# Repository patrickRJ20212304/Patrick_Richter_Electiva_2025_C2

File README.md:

# Patrick_Richter_Electiva_2025_C2

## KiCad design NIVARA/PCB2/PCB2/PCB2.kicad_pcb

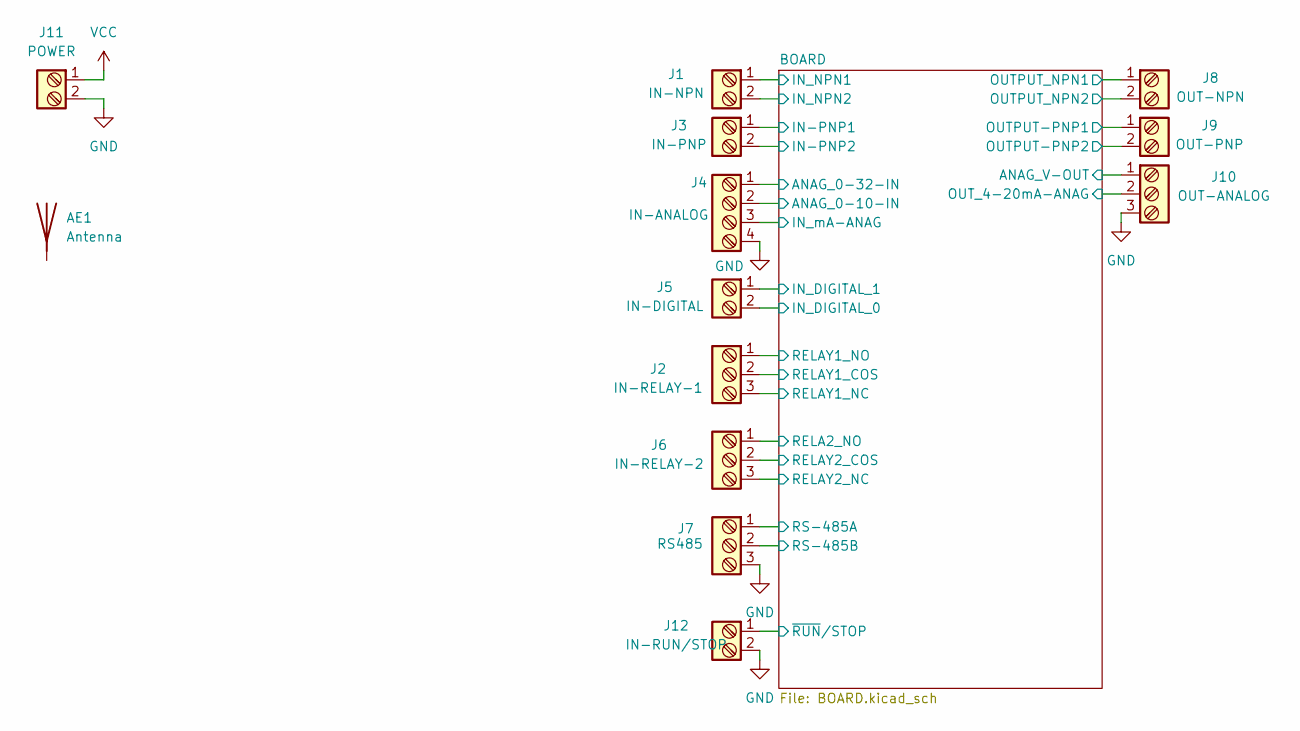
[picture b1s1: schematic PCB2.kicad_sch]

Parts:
AE1: Antenna
J1: IN-NPN; TerminalBlock_Phoenix_PT-1,5-2-5.0-H_1x02_P5.00mm_Horizontal
J2: IN-RELAY-1; TerminalBlock_Phoenix_PT-1,5-3-5.0-H_1x03_P5.00mm_Horizontal
J3: IN-PNP; TerminalBlock_Phoenix_PT-1,5-2-5.0-H_1x02_P5.00mm_Horizontal
J4: IN-ANALOG; TerminalBlock_Phoenix_PT-1,5-4-5.0-H_1x04_P5.00mm_Horizontal
J5: IN-DIGITAL; TerminalBlock_Phoenix_PT-1,5-2-5.0-H_1x02_P5.00mm_Horizontal
J6: IN-RELAY-2; TerminalBlock_Phoenix_PT-1,5-3-5.0-H_1x03_P5.00mm_Horizontal
J7: RS485; TerminalBlock_Phoenix_PT-1,5-3-5.0-H_1x03_P5.00mm_Horizontal
J8: OUT-NPN; TerminalBlock_Phoenix_PT-1,5-2-5.0-H_1x02_P5.00mm_Horizontal
J9: OUT-PNP; TerminalBlock_Phoenix_PT-1,5-2-5.0-H_1x02_P5.00mm_Horizontal
J10: OUT-ANALOG; TerminalBlock_Phoenix_PT-1,5-3-5.0-H_1x03_P5.00mm_Horizontal
J11: POWER; TerminalBlock_Phoenix_PT-1,5-2-5.0-H_1x02_P5.00mm_Horizontal
J12: IN-RUN/STOP; TerminalBlock_Phoenix_PT-1,5-2-5.0-H_1x02_P5.00mm_Horizontal

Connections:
/ANAG_V-OUT: J10.1
/BOARD/ANAG_0-10-IN: J4.2; also elsewhere on the board
/BOARD/ANAG_0-32-IN: J4.1; also elsewhere on the board
/BOARD/IN-PNP1: J3.1; also elsewhere on the board
/BOARD/IN-PNP2: J3.2; also elsewhere on the board
/BOARD/IN_DIGITAL_0: J5.2; also elsewhere on the board
/BOARD/IN_DIGITAL_1: J5.1; also elsewhere on the board
/BOARD/IN_NPN1: J1.1; also elsewhere on the board
/BOARD/IN_NPN2: J1.2; also elsewhere on the board
/BOARD/IN_mA-ANAG: J4.3; also elsewhere on the board
/BOARD/OUTPUT-PNP1: J9.1; also elsewhere on the board
/BOARD/OUTPUT-PNP2: J9.2; also elsewhere on the board
/BOARD/OUTPUT_NPN1: J8.1; also elsewhere on the board
/BOARD/OUTPUT_NPN2: J8.2; also elsewhere on the board
/BOARD/OUT_4-20mA-ANAG: J10.2; also elsewhere on the board
/BOARD/RELA2_NO: J6.1; also elsewhere on the board
/BOARD/RELAY1_COS: J2.2; also elsewhere on the board
/BOARD/RELAY1_NC: J2.3; also elsewhere on the board
/BOARD/RELAY1_NO: J2.1; also elsewhere on the board
/BOARD/RELAY2_COS: J6.2; also elsewhere on the board
/BOARD/RELAY2_NC: J6.3; also elsewhere on the board
/BOARD/RS-485A: J7.1; also elsewhere on the board
/BOARD/RS-485B: J7.2; also elsewhere on the board
/BOARD/~RUN/STOP: J12.1; also elsewhere on the board
GND: J4.4, J7.3, J10.3, J11.2, J12.2; also elsewhere on the board
VCC: J11.1; also elsewhere on the board

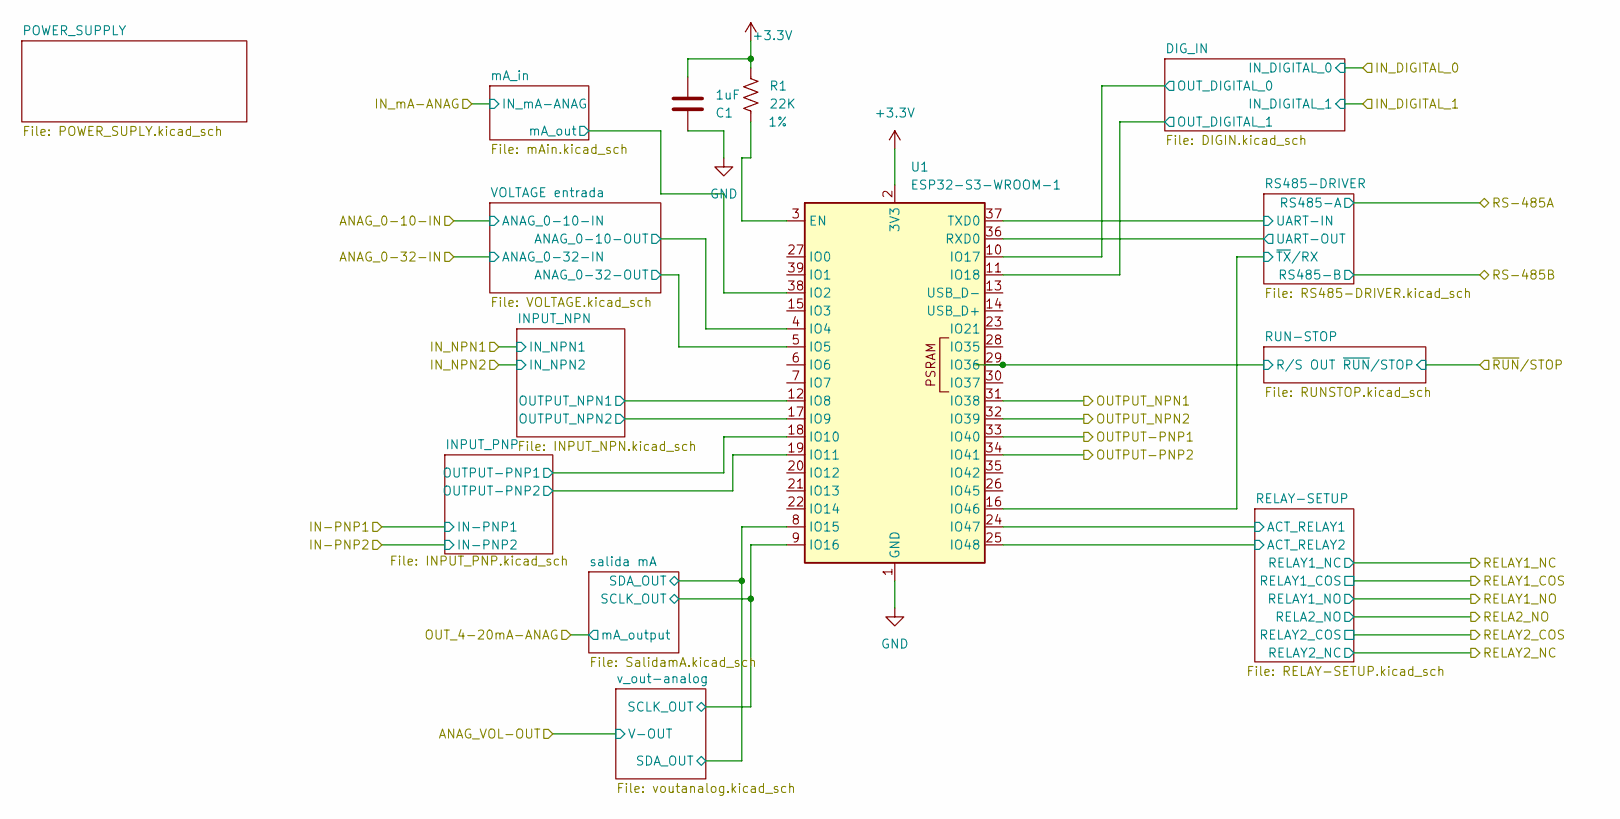
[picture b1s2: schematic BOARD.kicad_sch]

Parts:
C1: 1uF; C_0603_1608Metric; Voltage 10V
R1: 22K; R_0603; Tolerance 1%
U1: ESP32-S3-WROOM-1

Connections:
+3.3V: C1.2, R1.1, U1.2 (3V3); also elsewhere on the board
/BOARD/DIG_IN/OUT_DIGITAL_0: U1.10 (IO17); also elsewhere on the board
/BOARD/DIG_IN/OUT_DIGITAL_1: U1.11 (IO18); also elsewhere on the board
/BOARD/INPUT_NPN/OUTPUT_NPN1: U1.12 (IO8); also elsewhere on the board
/BOARD/INPUT_NPN/OUTPUT_NPN2: U1.17 (IO9); also elsewhere on the board
/BOARD/INPUT_PNP/OUTPUT-PNP1: U1.18 (IO10); also elsewhere on the board
/BOARD/INPUT_PNP/OUTPUT-PNP2: U1.19 (IO11); also elsewhere on the board
/BOARD/IN_mA-ANAG: U1.38 (IO2); also elsewhere on the board
/BOARD/OUTPUT-PNP1: U1.33 (IO40); also elsewhere on the board
/BOARD/OUTPUT-PNP2: U1.34 (IO41); also elsewhere on the board
/BOARD/OUTPUT_NPN1: U1.31 (IO38); also elsewhere on the board
/BOARD/OUTPUT_NPN2: U1.32 (IO39); also elsewhere on the board
/BOARD/RELAY-SETUP/ACT_RELAY1: U1.24 (IO47); also elsewhere on the board
/BOARD/RELAY-SETUP/ACT_RELAY2: U1.25 (IO48); also elsewhere on the board
/BOARD/RS485-DRIVER/UART-IN: U1.37 (TXD0); also elsewhere on the board
/BOARD/RS485-DRIVER/UART-OUT: U1.36 (RXD0); also elsewhere on the board
/BOARD/RS485-DRIVER/~TX/RX: U1.16 (IO46); also elsewhere on the board
/BOARD/VOLTAGE entrada/ANAG_0-10-OUT: U1.4 (IO4); also elsewhere on the board
/BOARD/VOLTAGE entrada/ANAG_0-32-OUT: U1.5 (IO5); also elsewhere on the board
/BOARD/salida mA/SCLK_OUT: U1.9 (IO16); also elsewhere on the board
/BOARD/salida mA/SDA_OUT: U1.8 (IO15); also elsewhere on the board
/BOARD/~RUN/STOP: U1.29 (IO36); also elsewhere on the board
GND: C1.1, U1.1 (GND), U1.40 (GND), U1.41 (GND); also elsewhere on the board
unnamed: R1.2, U1.3 (EN)

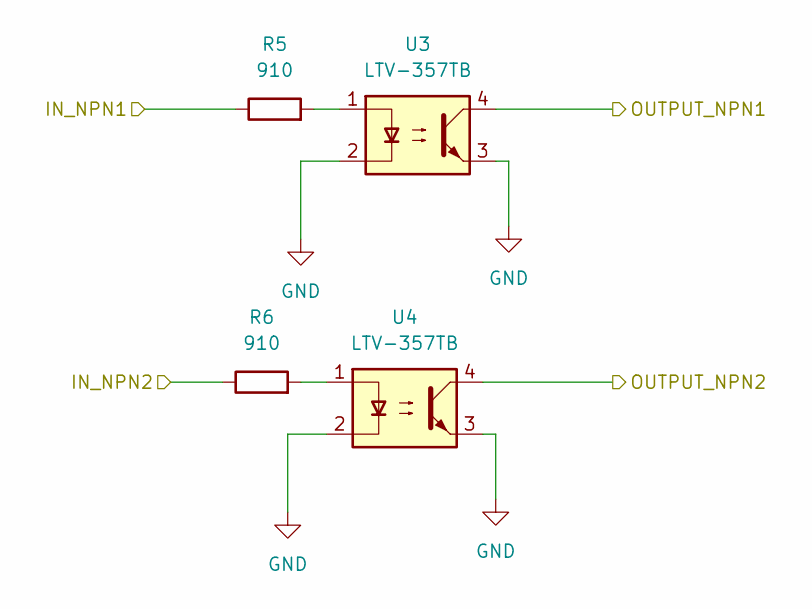
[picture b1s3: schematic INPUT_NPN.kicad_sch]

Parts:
R5, R6: 910; R_0603_1608Metric; LCSC# C114670
U3, U4: LTV-357TB; SO-4_4.4x3.6mm_P2.54mm

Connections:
/BOARD/INPUT_NPN/OUTPUT_NPN1: U3.4; also elsewhere on the board
/BOARD/INPUT_NPN/OUTPUT_NPN2: U4.4; also elsewhere on the board
/BOARD/IN_NPN1: R5.1; also elsewhere on the board
/BOARD/IN_NPN2: R6.1; also elsewhere on the board
GND: U3.2, U3.3, U4.2, U4.3; also elsewhere on the board
unnamed: R5.2, U3.1
unnamed: R6.2, U4.1

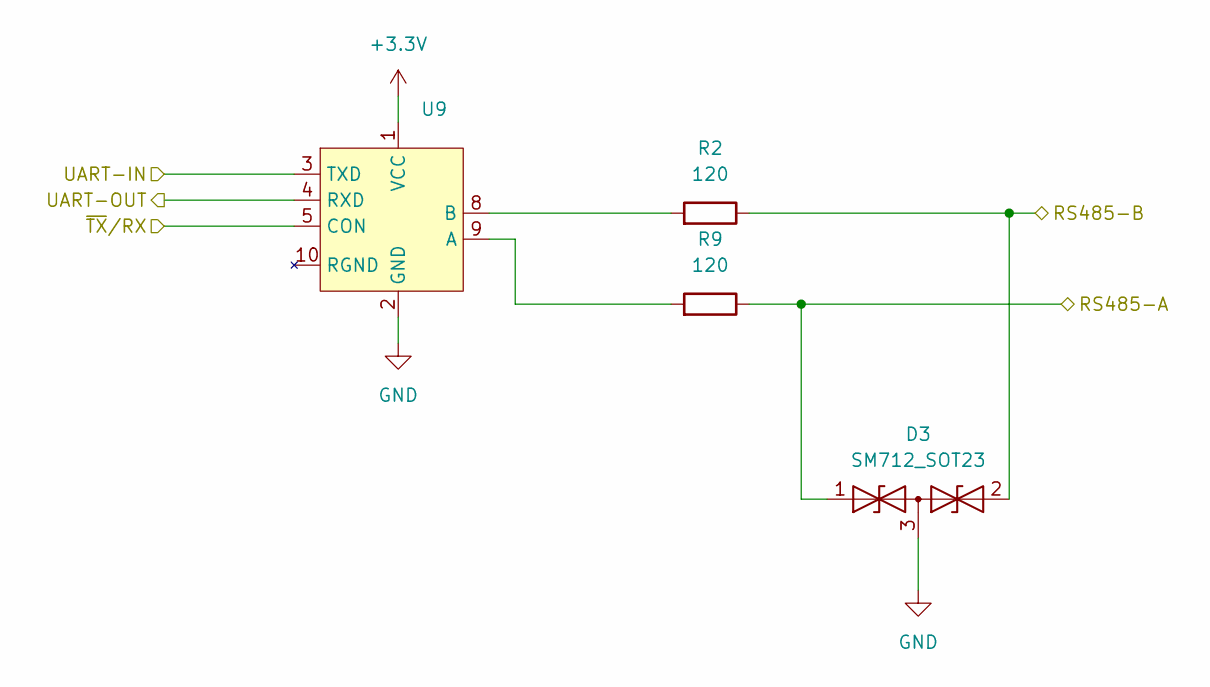
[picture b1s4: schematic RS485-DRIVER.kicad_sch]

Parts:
D3: SM712_SOT23; SOT-23
R2, R9: 120; R_0603_1608Metric
U9: RSM3485ECHT

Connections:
+3.3V: U9.1 (VCC); also elsewhere on the board
/BOARD/RS485-DRIVER/UART-IN: U9.3 (TXD); also elsewhere on the board
/BOARD/RS485-DRIVER/UART-OUT: U9.4 (RXD); also elsewhere on the board
/BOARD/RS485-DRIVER/~TX/RX: U9.5 (CON); also elsewhere on the board
/BOARD/RS-485A: D3.1 (A1), R9.2; also elsewhere on the board
/BOARD/RS-485B: D3.2 (A2), R2.2; also elsewhere on the board
GND: D3.3 (common), U9.2 (GND); also elsewhere on the board
unnamed: R9.1, U9.9 (A)
unnamed: R2.1, U9.8 (B)

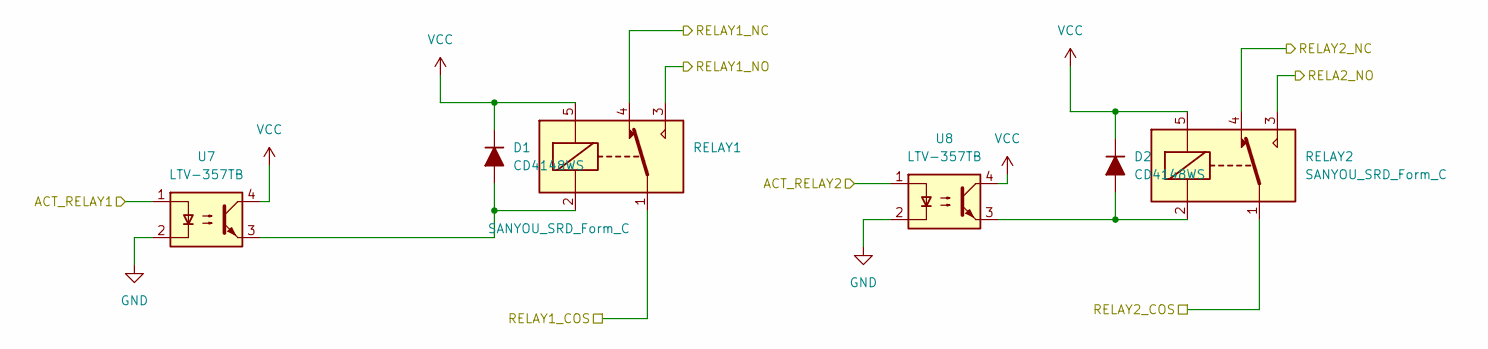
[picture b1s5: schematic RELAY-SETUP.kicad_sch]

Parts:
D1, D2: CD4148WS; D_0805_2012Metric
RELAY1, RELAY2: SANYOU_SRD_Form_C; Relay_SPDT_SANYOU_SRD_Series_Form_C
U7, U8: LTV-357TB; SO-4_4.4x3.6mm_P2.54mm

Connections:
/BOARD/RELA2_NO: RELAY2.3; also elsewhere on the board
/BOARD/RELAY1_COS: RELAY1.1; also elsewhere on the board
/BOARD/RELAY1_NC: RELAY1.4; also elsewhere on the board
/BOARD/RELAY1_NO: RELAY1.3; also elsewhere on the board
/BOARD/RELAY2_COS: RELAY2.1; also elsewhere on the board
/BOARD/RELAY2_NC: RELAY2.4; also elsewhere on the board
/BOARD/RELAY-SETUP/ACT_RELAY1: U7.1; also elsewhere on the board
/BOARD/RELAY-SETUP/ACT_RELAY2: U8.1; also elsewhere on the board
GND: U7.2, U8.2; also elsewhere on the board
unnamed: D1.2 (A), RELAY1.2, U7.3
unnamed: D2.2 (A), RELAY2.2, U8.3
VCC: D1.1 (K), D2.1 (K), RELAY1.5, RELAY2.5, U7.4, U8.4; also elsewhere on the board

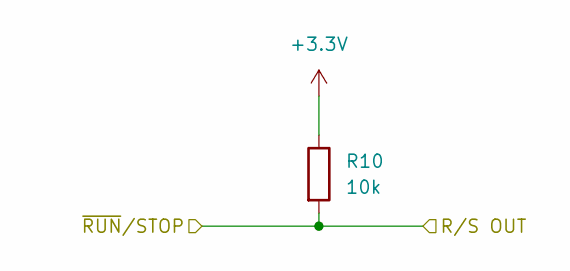
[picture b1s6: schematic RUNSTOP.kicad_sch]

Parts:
R10: 10k; R_0603

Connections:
+3.3V: R10.1; also elsewhere on the board
/BOARD/~RUN/STOP: R10.2; also elsewhere on the board

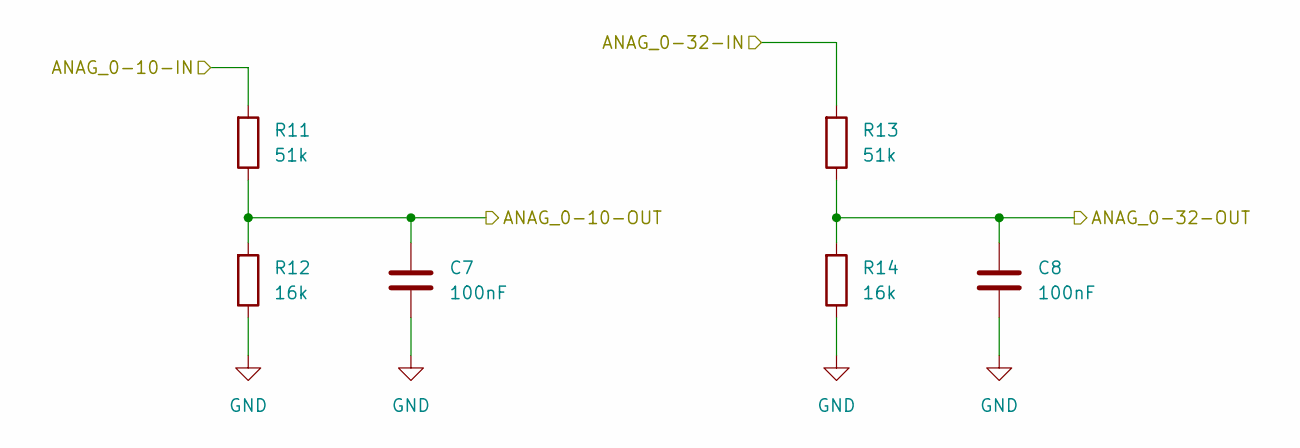
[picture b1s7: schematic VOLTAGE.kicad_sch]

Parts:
C7, C8: 100nF; C_0603_1608Metric
R11, R13: 51k; R_0603_1608Metric
R12, R14: 16k; R_0603_1608Metric

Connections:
/BOARD/ANAG_0-10-IN: R11.1; also elsewhere on the board
/BOARD/ANAG_0-32-IN: R13.1; also elsewhere on the board
/BOARD/VOLTAGE entrada/ANAG_0-10-OUT: C7.1, R11.2, R12.1; also elsewhere on the board
/BOARD/VOLTAGE entrada/ANAG_0-32-OUT: C8.1, R13.2, R14.1; also elsewhere on the board
GND: C7.2, C8.2, R12.2, R14.2; also elsewhere on the board

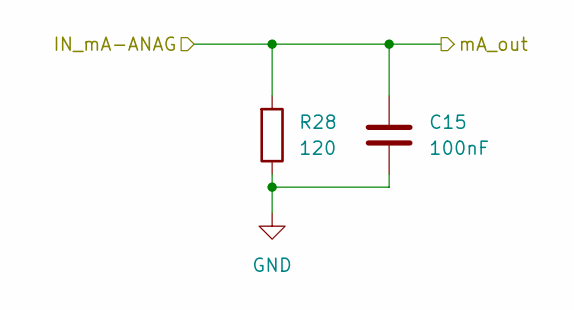
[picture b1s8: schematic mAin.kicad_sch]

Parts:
C15: 100nF; C_0603_1608Metric
R28: 120; R_0603_1608Metric

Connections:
/BOARD/IN_mA-ANAG: C15.1, R28.1; also elsewhere on the board
GND: C15.2, R28.2; also elsewhere on the board

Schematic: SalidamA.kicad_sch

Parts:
C9, C11: 1uF; C_0603_1608Metric
C10: 220pF; C_0603_1608Metric
C12: 0.1uF; C_0603_1608Metric
D4: 1N4007; D_0201_0603Metric
D6, D7: SMF24A; D_0201_0603Metric; LCSC# C7495269
GP2: SSOP-10_3.9x4.9mm_P1.00mm
JP2, JP3, JP4: SolderJumper_2_Open; SolderJumper-2_P1.3mm_Open_RoundedPad1.0x1.5mm
Q1: AO3401A; SOT-23
R15, R16: 4.7k; R_0603_1608Metric
R17: 100k; R_0603
R18: 15; R_0603
R19: 2.5k; R_0603_1608Metric
R20, R21, R22: 10k; R_0603_1608Metric

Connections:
+3.3V: R15.1, R16.1; also elsewhere on the board
/BOARD/OUT_4-20mA-ANAG: D4.1 (K); also elsewhere on the board
/BOARD/salida mA/SCLK_OUT: GP2.1 (SCLK), R16.2; also elsewhere on the board
/BOARD/salida mA/SDA_OUT: GP2.2 (SDA), R15.2; also elsewhere on the board
GND: C9.2, C10.2, C11.2, C12.2, D6.2 (A2), GP2.6 (GND), JP2.1 (A), JP3.1 (A), JP4.1 (A), R17.2, R19.2; also elsewhere on the board
unnamed: D4.2 (A), R18.2
unnamed: C12.1, D6.1 (A1), Q1.3 (D), R18.1
unnamed: C11.1, D7.2 (A2), Q1.1 (G), R17.1
unnamed: GP2.3 (A0), JP4.2 (B), R22.2
unnamed: GP2.4 (A1), JP3.2 (B), R21.2
unnamed: GP2.9 (A2), JP2.2 (B), R20.2
unnamed: C10.1, GP2.7 (SET), R19.1
unnamed: C9.1, GP2.10 (V5V), R20.1, R21.1, R22.1
VCC: D7.1 (A1), GP2.5 (VCC); also elsewhere on the board
i_out: GP2.8 (IOUT), Q1.2 (S)

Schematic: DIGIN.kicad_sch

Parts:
R24, R27: 910; R_0603_1608Metric; LCSC# C114670
R25, R26: 412; R_0603_1608Metric
U10, U11: LTV-357TB; SO-4_4.4x3.6mm_P2.54mm

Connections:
+3.3V: R25.2, R26.2; also elsewhere on the board
/BOARD/DIG_IN/OUT_DIGITAL_0: R25.1, U10.4; also elsewhere on the board
/BOARD/DIG_IN/OUT_DIGITAL_1: R26.1, U11.4; also elsewhere on the board
/BOARD/IN_DIGITAL_0: U10.2; also elsewhere on the board
/BOARD/IN_DIGITAL_1: U11.2; also elsewhere on the board
GND: U10.3, U11.3; also elsewhere on the board
unnamed: R24.2, U11.1
unnamed: R27.2, U10.1
VCC: R24.1, R27.1; also elsewhere on the board

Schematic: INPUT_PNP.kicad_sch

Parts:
R7, R8: 910; R_0603_1608Metric; LCSC# C114670
U5, U6: LTV-357TB; SO-4_4.4x3.6mm_P2.54mm

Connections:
/BOARD/IN-PNP1: R8.1; also elsewhere on the board
/BOARD/IN-PNP2: R7.1; also elsewhere on the board
/BOARD/INPUT_PNP/OUTPUT-PNP1: U6.4; also elsewhere on the board
/BOARD/INPUT_PNP/OUTPUT-PNP2: U5.4; also elsewhere on the board
GND: U5.2, U5.3, U6.2, U6.3; also elsewhere on the board
unnamed: R7.2, U5.1
unnamed: R8.2, U6.1

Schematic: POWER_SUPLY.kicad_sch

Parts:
C2, C6: 22uF; C_0805_2012Metric; voltage 10V
C3: 10uF; C_1206_3216Metric; voltage 50V
C4: 100nF; C_0603_1608Metric; Voltage 50V
C5: 100PF; C_0603_1608Metric; Voltage 50V
JP1: SolderJumper_2_Open; SolderJumper-2_P1.3mm_Open_RoundedPad1.0x1.5mm
L1: 6.8uH; L_Bourns-SRN6028
R3, R4: 22k; R_0603_1608Metric
TP1, TP2, TP3, TP4: TestPoint; Pin_D1.0mm_L10.0mm
U2: AP63200WU; TSOT-23-6

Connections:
+3.3V: JP1.2 (B), TP1.1; also elsewhere on the board
GND: C3.2, R4.2, U2.4 (GND); also elsewhere on the board
unnamed: C2.1, C5.2, C6.1, JP1.1 (A), L1.2, R3.1, TP2.1
unnamed: C4.1, U2.6 (BST)
unnamed: C2.2, C5.1, C6.2, R3.2, R4.1, TP3.1, U2.1 (FB)
unnamed: C4.2, L1.1, U2.5 (SW)
VCC: C3.1, TP4.1, U2.2 (EN), U2.3 (IN); also elsewhere on the board

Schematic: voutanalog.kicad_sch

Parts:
C13: 1uF; C_0603_1608Metric
C14: 100nF; C_0603_1608Metric
D5: SMF24A; D_SMF; LCSC# C7495269
GP8201S1: OnSemi_Micro8
R23: 10k; R_0603_1608Metric

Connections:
/BOARD/ANAG_VOL-OUT: C14.1, D5.1 (A1), GP8201S1.6 (VOUT)
/BOARD/salida mA/SCLK_OUT: GP8201S1.1 (SCLK); also elsewhere on the board
/BOARD/salida mA/SDA_OUT: GP8201S1.2 (SDA); also elsewhere on the board
GND: C13.2, C14.2, D5.2 (A2), GP8201S1.5 (GND); also elsewhere on the board
unnamed: C13.1, GP8201S1.7 (SEL), R23.1
unnamed: GP8201S1.8 (V5V), R23.2
VCC: GP8201S1.4 (VCC); also elsewhere on the board

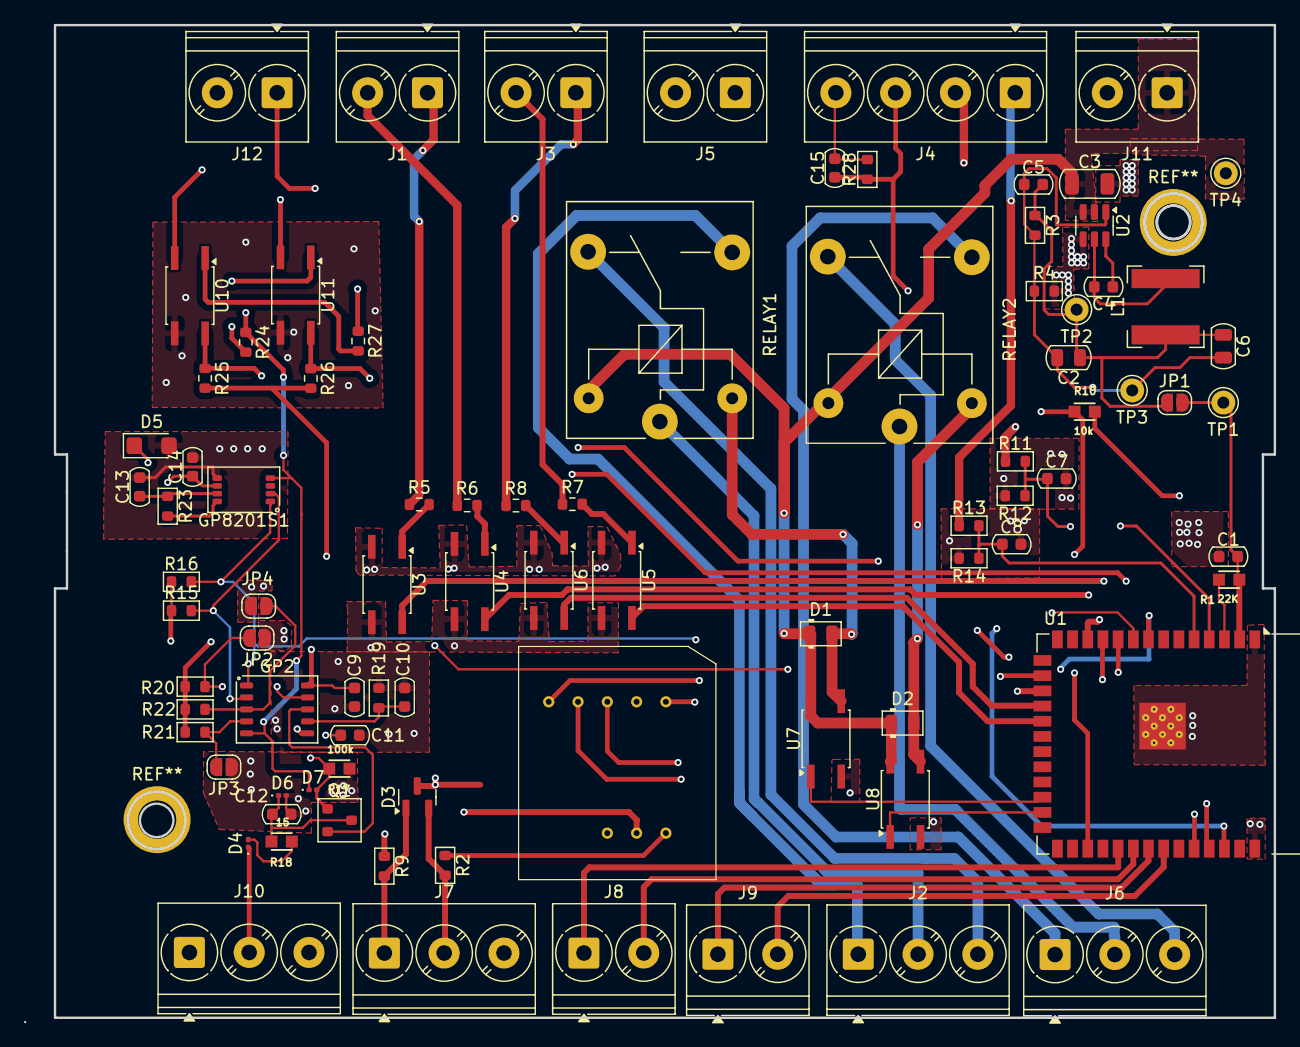
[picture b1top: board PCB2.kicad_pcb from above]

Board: 4 copper layers, 104.5 x 83.3 mm, 87 parts (0 on the bottom side), 68 nets.

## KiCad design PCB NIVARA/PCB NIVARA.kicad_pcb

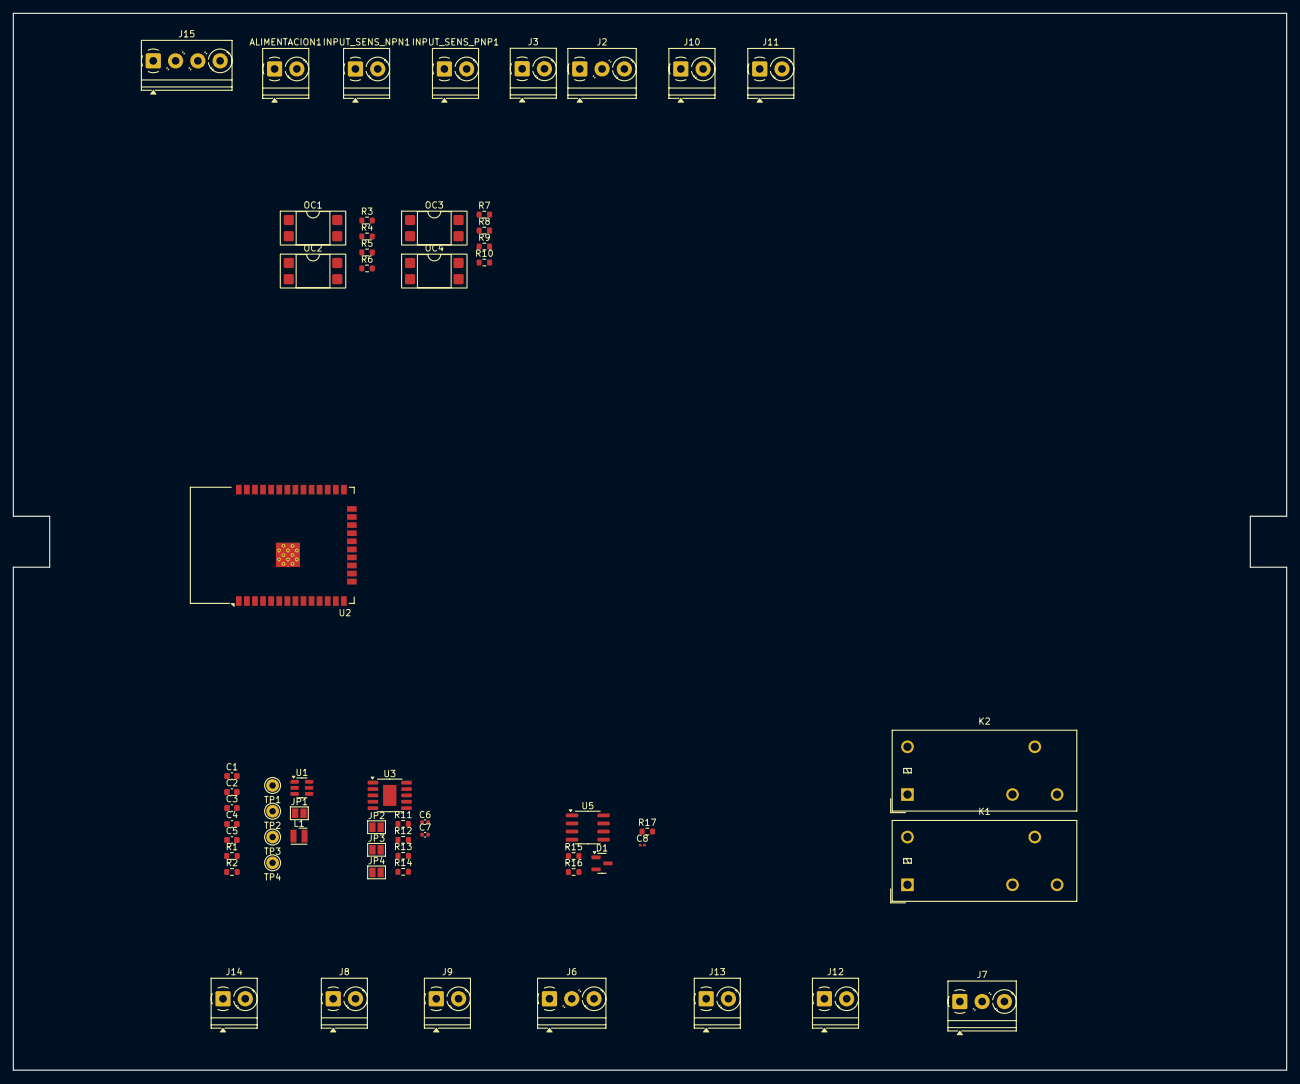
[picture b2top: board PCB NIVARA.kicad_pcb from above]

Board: 2 copper layers, 200.0 x 166.0 mm, 60 parts (0 on the bottom side), 27 nets, no tracks yet.

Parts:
ALIMENTACION1: 5-24V; TerminalBlock_Phoenix_PT-1,5-2-3.5-H_1x02_P3.50mm_Horizontal
C1: 10uF; C_0603_1608Metric
C2: 100nF; C_0603_1608Metric
C3: 10pF; C_0603_1608Metric
C4, C5: 22uF; C_0603_1608Metric
C6: 220pF; C_0402_1005Metric
C7: 1uF; C_0402_1005Metric
C8: 100nF; C_0201_0603Metric
D1: SM712_SOT23; SOT-23
INPUT_SENS_NPN1: TerminalBlock_Phoenix_PT-1,5-2-3.5-H_1x02_P3.50mm_Horizontal
INPUT_SENS_PNP1: TerminalBlock_Phoenix_PT-1,5-2-3.5-H_1x02_P3.50mm_Horizontal
J2: RS485; TerminalBlock_Phoenix_PT-1,5-3-3.5-H_1x03_P3.50mm_Horizontal
J3, J10: ENTRADA 0-32; TerminalBlock_Phoenix_PT-1,5-2-3.5-H_1x02_P3.50mm_Horizontal
J6, J7: relay1 out; TerminalBlock_Phoenix_PT-1,5-3-3.5-H_1x03_P3.50mm_Horizontal
J8: Salida npn; TerminalBlock_Phoenix_PT-1,5-2-3.5-H_1x02_P3.50mm_Horizontal
J9: Salida pnp; TerminalBlock_Phoenix_PT-1,5-2-3.5-H_1x02_P3.50mm_Horizontal
J11: 4-20mA; TerminalBlock_Phoenix_PT-1,5-2-3.5-H_1x02_P3.50mm_Horizontal
J12: salida 0-10; TerminalBlock_Phoenix_PT-1,5-2-3.5-H_1x02_P3.50mm_Horizontal
J13: salida 0-32; TerminalBlock_Phoenix_PT-1,5-2-3.5-H_1x02_P3.50mm_Horizontal
J14: salida 4-20mA; TerminalBlock_Phoenix_PT-1,5-2-3.5-H_1x02_P3.50mm_Horizontal
J15: INTERRUPTOR; TerminalBlock_Phoenix_PT-1,5-4-3.5-H_1x04_P3.50mm_Horizontal
JP1, JP2, JP3, JP4: SolderJumper_2_Open; SolderJumper-2_P1.3mm_Open_Pad1.0x1.5mm
K1, K2: G2RL-1; Relay_SPDT_Omron_G2RL-1
L1: L_Iron; L_Wurth_WE-LQSH-2512
OC1, OC2, OC3, OC4: PC817; DIP-4_W7.62mm_SMDSocket_SmallPads
R1, R2: 22k; R_0603_1608Metric
R3, R4, R7, R8: 1K; R_0603_1608Metric
R5, R6, R9, R10: 550; R_0603_1608Metric
R11, R12, R13: 10k; R_0603_1608Metric
R14: 2.5k; R_0603_1608Metric
R15, R16, R17: 10K; R_0603_1608Metric
TP1, TP2, TP3, TP4: TestPoint; Pin_D1.0mm_L10.0mm
U1: AP63203WU; TSOT-23-6
U2: ESP32-WROOM-32D
U3: SSOP-10-1EP_3.9x4.9mm_P1mm_EP2.1x3.3mm
U5: SP3485EN; SOIC-8_3.9x4.9mm_P1.27mm

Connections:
+3.3V: C8.2, JP1.1 (A), R5.2, R6.2, R9.2, R10.2, R15.2, TP4.1, U5.8 (VCC)
/BOARD/E-NPN 0: INPUT_SENS_NPN1.1, R3.1
/BOARD/E-NPN 1: INPUT_SENS_NPN1.2, R4.1
/BOARD/E-PNP 0: INPUT_SENS_PNP1.1, R7.1
/BOARD/E-PNP 1: INPUT_SENS_PNP1.2, R8.1
/BOARD/RS485/RS-485 A: D1.2 (A2), R15.1, R16.2, U5.6 (A)
/BOARD/RS485/RS-485 B: D1.1 (A1), R16.1, R17.2, U5.7 (B)
/BOARD/RS485/~TX/RX: U5.2 (~RE), U5.3 (DE)
/BOARD/S-NPN 0: J8.1, OC1.4, R5.1
/BOARD/S-NPN 1: J8.2, OC2.4, R6.1
/BOARD/S-PNP 0: J9.1, OC3.4, R9.1
/BOARD/S-PNP 1: J9.2, OC4.4, R10.1
GND: ALIMENTACION1.2, C1.2, C4.1, C5.1, C6.2, C7.2, C8.1, D1.3 (common), J2.3, J3.2, J10.2, J11.2, J12.2, J13.2, J14.2, J15.4, JP2.1 (A), JP3.1 (A), JP4.1 (A), OC1.2, OC1.3, OC2.2, OC2.3, OC3.2, OC3.3, OC4.2, OC4.3, R2.1, R14.2, R17.1, U1.4 (GND), U2.1 (GND), U2.15 (GND), U2.38 (GND), U2.39 (GND), U3.6 (GND), U5.5 (GND)
unnamed: C3.2, C4.2, C5.2, JP1.2 (B), L1.2, R1.2, TP2.1
unnamed: JP2.2 (B), R11.2, U3.9 (A2)
unnamed: JP3.2 (B), R12.2, U3.4 (A1)
unnamed: JP4.2 (B), R13.2, U3.3 (A0)
unnamed: OC1.1, R3.2
unnamed: OC2.1, R4.2
unnamed: OC3.1, R7.2
unnamed: OC4.1, R8.2
unnamed: C2.1, U1.6 (BST)
unnamed: C3.1, R1.1, R2.2, TP1.1, U1.1 (FB)
unnamed: C2.2, L1.1, U1.5 (SW)
unnamed: C6.1, R14.1, U3.7 (SET)
unnamed: C7.1, R11.1, R12.1, R13.1, U3.10 (V5V)
VCC: ALIMENTACION1.1, C1.1, K1.A1, K2.A1, TP3.1, U1.2 (EN), U1.3 (IN), U3.5 (VCC)
